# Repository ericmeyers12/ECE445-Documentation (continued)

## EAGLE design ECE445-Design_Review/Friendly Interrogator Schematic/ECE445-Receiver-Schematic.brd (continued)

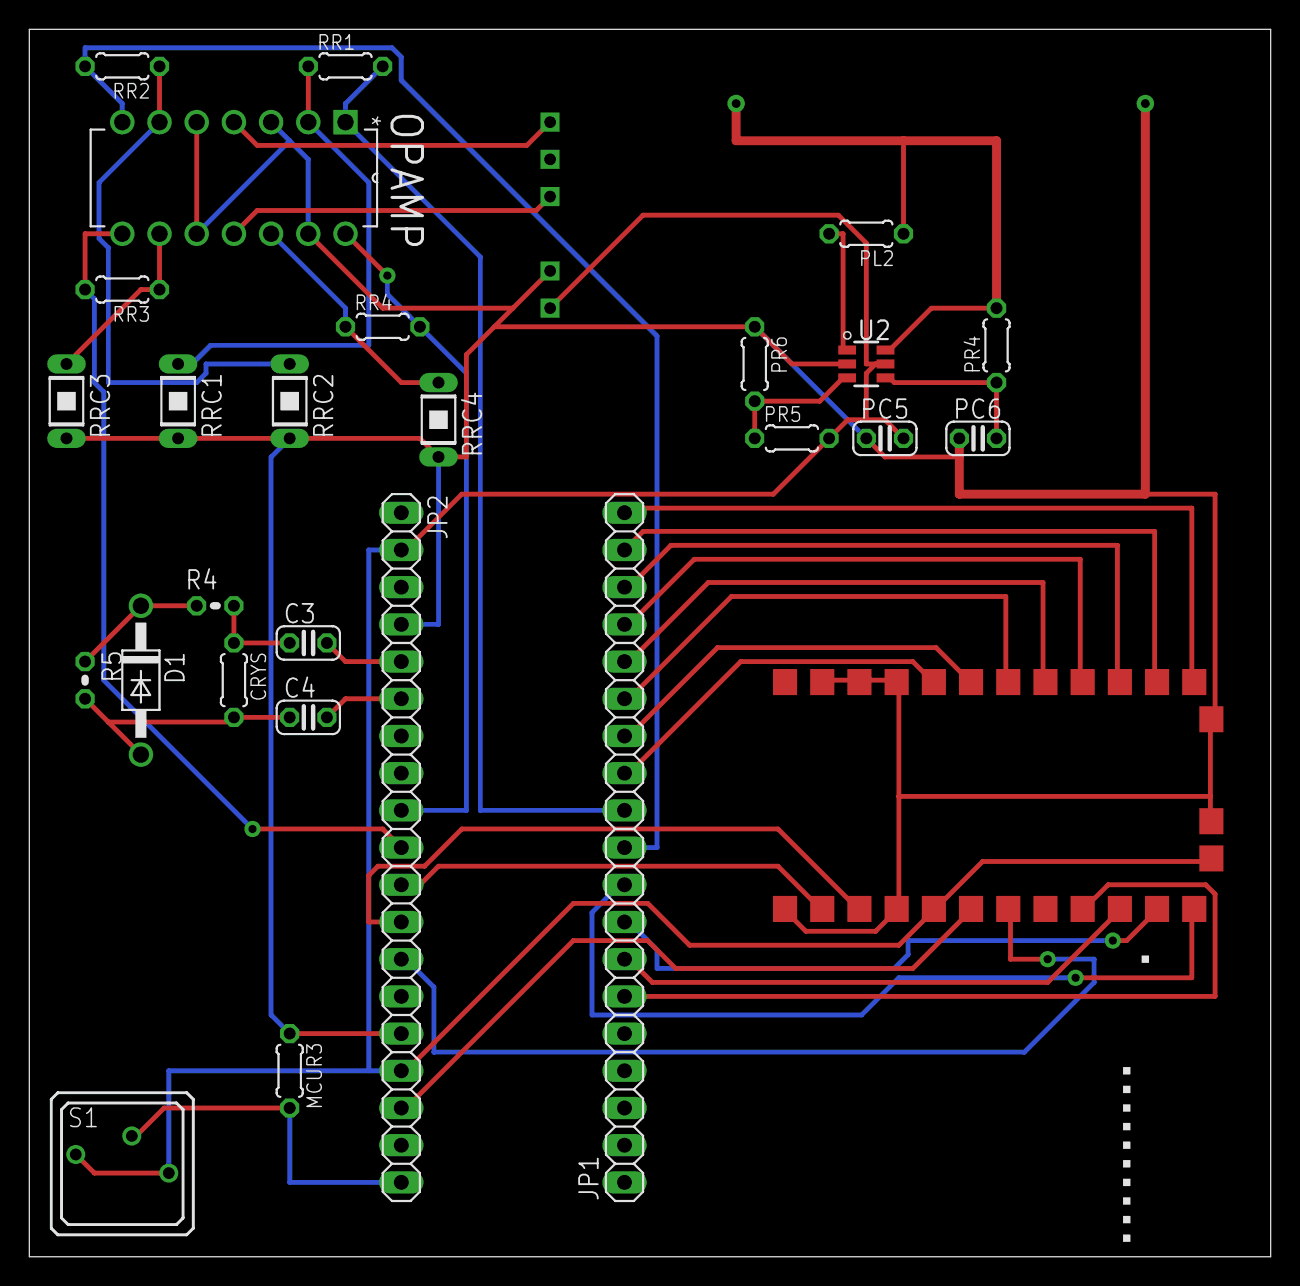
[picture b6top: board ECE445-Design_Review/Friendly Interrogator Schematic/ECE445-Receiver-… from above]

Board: 2 copper layers, 84.8 x 83.8 mm, 39 parts (0 on the bottom side), 38 nets.

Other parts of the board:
U$13: PDM1-S3-D12-S

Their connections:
3.3V: U$13.1; also elsewhere on the board
+10V: U$13.5; also elsewhere on the board
-10V: U$13.3; also elsewhere on the board
GND: U$13.2; also elsewhere on the board

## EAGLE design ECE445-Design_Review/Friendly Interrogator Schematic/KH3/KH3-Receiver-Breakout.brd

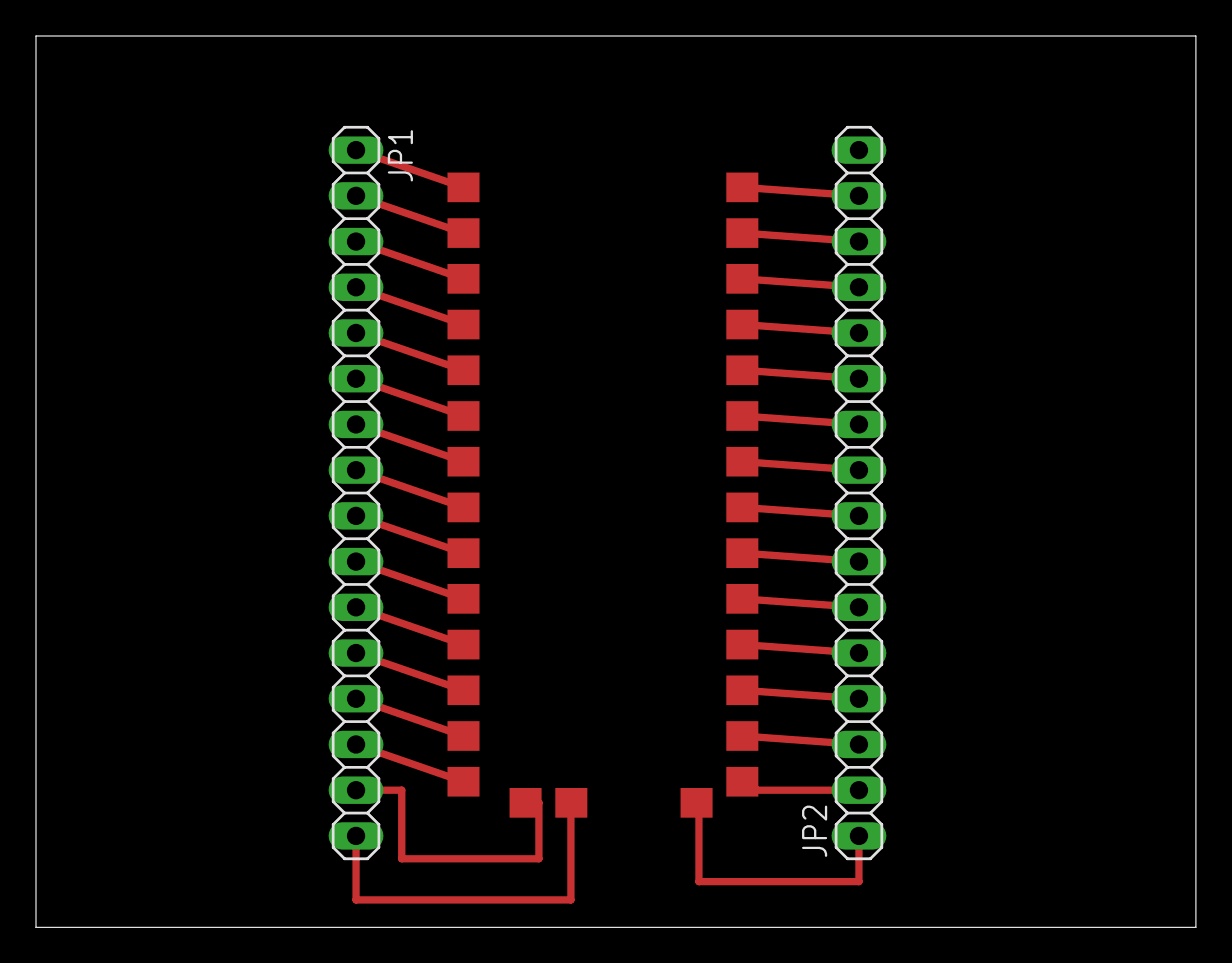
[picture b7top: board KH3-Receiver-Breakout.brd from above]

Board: 2 copper layers, 64.4 x 49.5 mm, 3 parts (0 on the bottom side), 31 nets.

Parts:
JP1, JP2: 1X16
U$1: KH3-RXM-LINX-315

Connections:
unnamed: JP1.3, U$1.3
unnamed: JP1.4, U$1.4
unnamed: JP1.5, U$1.5
unnamed: JP1.6, U$1.6
unnamed: JP1.7, U$1.7
unnamed: JP1.8, U$1.8
unnamed: JP1.9, U$1.9
unnamed: JP1.10, U$1.10
unnamed: JP1.11, U$1.11
unnamed: JP1.12, U$1.12
unnamed: JP1.13, U$1.13
unnamed: JP1.14, U$1.14
unnamed: JP2.14, U$1.27
unnamed: JP1.16, U$1.30
unnamed: JP2.13, U$1.26
unnamed: JP2.12, U$1.25
unnamed: JP2.11, U$1.24
unnamed: JP2.10, U$1.23
unnamed: JP2.9, U$1.22
unnamed: JP2.8, U$1.21
unnamed: JP2.7, U$1.20
unnamed: JP2.6, U$1.19
unnamed: JP2.5, U$1.18
unnamed: JP2.4, U$1.17
unnamed: JP2.3, U$1.16
unnamed: JP2.2, U$1.15
unnamed: JP2.1, U$1.31
unnamed: JP1.15, U$1.29
unnamed: JP2.15, U$1.28
unnamed: JP1.2, U$1.2
unnamed: JP1.1, U$1.1

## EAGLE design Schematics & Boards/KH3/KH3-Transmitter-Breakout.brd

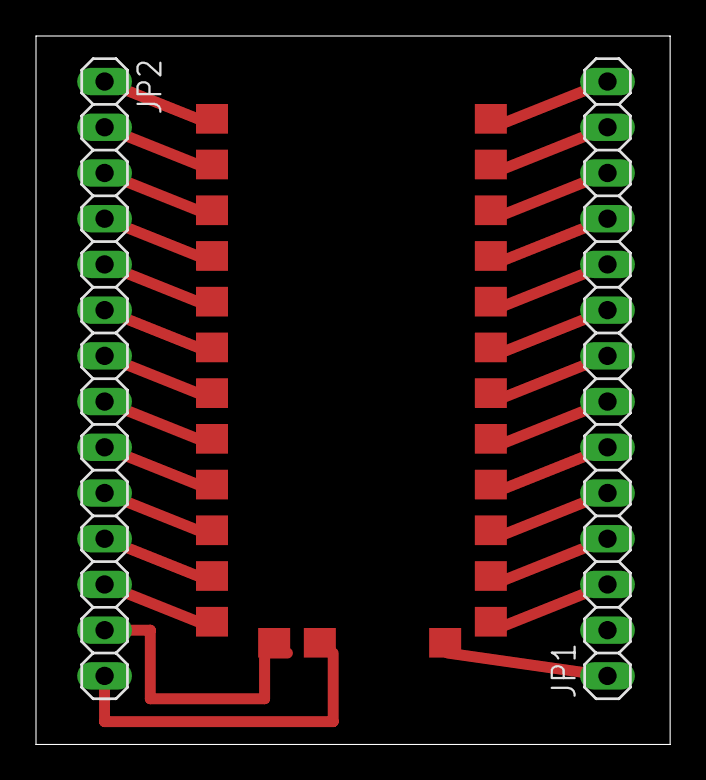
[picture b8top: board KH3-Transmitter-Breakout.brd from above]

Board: 2 copper layers, 35.2 x 39.4 mm, 3 parts (0 on the bottom side), 27 nets.

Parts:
JP1, JP2: 1X14
U$1: LINX-KH3-TRANSMITTER

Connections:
unnamed: JP2.1, U$1.1
unnamed: JP2.2, U$1.2
unnamed: JP2.3, U$1.3
unnamed: JP2.4, U$1.4
unnamed: JP2.5, U$1.5
unnamed: JP2.6, U$1.6
unnamed: JP2.7, U$1.7
unnamed: JP2.8, U$1.8
unnamed: JP2.9, U$1.9
unnamed: JP2.10, U$1.10
unnamed: JP2.11, U$1.11
unnamed: JP2.12, U$1.12
unnamed: JP2.14, U$1.14
unnamed: JP1.14, U$1.27
unnamed: JP1.13, U$1.26
unnamed: JP1.12, U$1.25
unnamed: JP1.11, U$1.24
unnamed: JP1.10, U$1.23
unnamed: JP1.9, U$1.22
unnamed: JP1.8, U$1.21
unnamed: JP1.7, U$1.20
unnamed: JP1.6, U$1.19
unnamed: JP1.5, U$1.18
unnamed: JP1.4, U$1.17
unnamed: JP1.3, U$1.16
unnamed: JP1.1, U$1.15
unnamed: JP2.13, U$1.13

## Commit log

2016-02-08 "Initial Commit"
2016-02-09 Modified tolerance analysis, filled out some of labor. Parts needs work
2016-02-10 "Added labor/cost analysis, refined requirements, made slight format tweaks"
2016-02-10 "Made some slight changes to requirements"
2016-02-11 Add calculations for laser milliwatts
2016-02-11 Fix calculation
2016-02-11 "Updating My End"
2016-02-11 Some minor changes
2016-02-11 Add acronym
2016-02-11 "Proposal Submission - DONE MOTHERFUCKER"
2016-02-16 "Mock Design Review Initial Commit"
2016-02-17 "Mock Design Review - added circuit schematic, started working on block descriptions"
2016-02-17 "Added block diagram, added some block descriptions, started on requirements"
2016-02-18 Add safety concerns and more info on laser pointer
2016-02-18 Add plot
2016-02-18 Move to cm
2016-02-18 Add nohd vs power png
2016-02-18 "Added some stuff for block descriptions, changed battery size"
2016-02-19 "Design Review Template Complete, initial commit"
2016-02-21 "Committing a bunch of changes to overall structure"
2016-02-24 "Eagle Files Added, major updates to design review document"
2016-02-25 Add kh3 library
2016-02-25 Finish schematic for friendly target
2016-02-27 Add tolerance analysis and finish friendly schematic
2016-02-27 "BREAKING SHIT BRB"
2016-02-27 Add table
2016-02-27 More on MCU connections
2016-02-28 "No Connect Library"
2016-02-28 Power calculations
2016-02-28 Remove bad files
2016-02-28 "Commit test"
2016-02-28 Add power module stuff back
2016-02-28 Added some power calculations
2016-02-29 Fuck this project. added some shit about encryption, updated rtc functionality and reviewed block diagram/description.
2016-02-29 Added a fuckto-like a page and a half-n of citations
2016-02-29 All thats left to do is finish up parts, schedule, schematics, software flow, simulations, and make it look a bit more pretty
2016-02-29 Added some changes to the software flow
2016-03-01 Added Parts Cost
2016-03-02 Some stuff
2016-03-02 Add circuit schematics and a whole bunch of other shit
2016-03-02 Final Merge Maybe
2016-03-02 Add image sources
2016-03-02 Final Merge Maybe?????? FUCK THIS PROJECT
2016-03-02 Proof read
2016-03-02 Final Commit. Submitted.
2016-03-02 Update schematics
2016-03-09 adding updated schedule, updated ethics section
2016-03-09 added progress report sheet
2016-03-10 Design Review Addendum Submission
2016-03-15 Added my revision of schematics and boards
2016-03-16 Initial Commit Software
2016-03-17 added RST line to schematic
2016-03-17 Adding schematics
2016-03-21 Added some files that somehow got removed in last merge
2016-03-23 Finish schematic
2016-03-23 Initial PCB Revision Submitted
2016-03-23 Some updates to Schematics and Boards - added all files into consolidated place
2016-03-23 Software section almost written, need to write some unit tests for 40kHz signal
2016-03-24 Added Individual Progress Report
2016-03-27 Add individual progress report
2016-03-27 Individual Progress stash fix?
2016-03-27 Individual Progress Report Eric Done
2016-04-04 Added new software components
2016-04-05 Breakout revision for friendly target
2016-04-05 Power to da msp
2016-04-07 Commit software
2016-04-08 software from 4/7
2016-04-08 Basic idea for receiving fleshed out
2016-04-08 Added new revision of interrogator board
2016-04-09 Final PCB
2016-04-09 Eric Boards
2016-04-09 Software additions
2016-04-11 Remove shorts and dimensions
2016-04-11 Friendly Target Software Added
2016-04-13 noah software changes to adc photo program
2016-04-14 Pushed noah software
2016-04-14 Lightup on valid transmission
2016-04-20 Final Project Proposal
2016-04-20 Final Report Template
2016-04-23 Count upward
2016-04-24 Interrogator updates
2016-04-25 Yesterday's work
2016-04-25 More shit
2016-04-28 Final Report started, intro almost done
2016-04-28 More Final Project Documentation - added more sections to template
2016-04-28 Push algorithms and some other stuff
2016-04-28 Rename algorithm
2016-04-28 Small change to algorithm 2
2016-04-28 Push packet counting psuedocode
2016-04-28 AAnnnnd some more stuff
2016-04-28 merge
2016-04-30 Basic framework for updating currents
2016-05-01 need to work on game logic
2016-05-01 added some cost analysis stuff, added some more verifications
2016-05-02 Paste mine next to other ethics
2016-05-02 Add pictures to adjustable laser
2016-05-02 Fix target power
2016-05-03 add images
2016-05-04 Fix Eric's change on radius
2016-05-04 Errata
2016-05-04 Safety bullshit
2016-05-04 changed tenses
2016-05-04 Fix safety again
2016-05-04 Some minor shit
2016-05-04 FINAL COMMIT. PROJECT FINISHED
